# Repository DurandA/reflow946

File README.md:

# Reflow946

The Reflow946 is a Bluetooth LE temperature controller for the 946C electronic hot plate. Using this controller, a reflow profile can be programmed from your web browser using the [Web Bluetooth](https://webbluetoothcg.github.io/web-bluetooth/) API. You can use preset profiles (e.g. for lead-free or leaded soldering) or create a custom profile for a perfect cheese fondue. 🫕

The controller board is intended to replace the original controller board. It is **only compatible with the 3 buttons variant** pictured above (see this [teardown](https://youtu.be/Gv2sRJ9y_Ok)). Please send a PR if you adapted the design to a new variant.

## Hardware

The controller is based on a ESP32 module with an IPEX antenna. Since the metal case acts as a Faraday cage, the BLE signal can be improved by taping an antenna outside of the case.

### Front

### Back

## Status

- [x] Temperature control
  - [x] Temperature control using the front panel
  - [x] [BLE GATT service](https://github.com/DurandA/reflow946-firmware/wiki/GATT-Services) for temperature control
- [x] Reflow profile programming
  - [x] [BLE GATT service](https://github.com/DurandA/reflow946-firmware/wiki/GATT-Services) for reflow profiles
  - [x] [Web Bluetooth application](https://duranda.github.io/reflow946/)

## Credits

* Arnaud Durand - Orignal design
* Elías Rodríguez Martín - Revision 1.1, conversion to KiCad

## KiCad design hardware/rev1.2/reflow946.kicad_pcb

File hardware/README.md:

# Hardware

The Reflow946 hardware design is available on [https://easyeda.com/DurandA/reflow](https://easyeda.com/DurandA/reflow).

Contributions in converting the project to KiCad are welcome.

## Revision 1.0

### ESP32 module variants

⚠️ There are 85°C and 105°C variants of the ESP32-WROOM-32U(E) module. When heating stuff with a large termal mass, the temperature inside the case can largely exceed 85°C, causing glitches and reboots of the ESP32. It is advised to use the H version of the module.

### BOM

| Name | Designator | Footprint | Quantity | Supplier |
|---|---|---|---|---|
| MOC3041M | U1 | DIP-6_L8.5-W6.4-P2.54-LS7.6-BL | 1 | [LCSC](https://lcsc.com/product-detail/C8921.html) |
| ESP32-WROOM-32UE-H4 | U2 | WIFIM-SMD_39P-L19.2-W18.0-P1.27 | 1 | [LCSC](https://lcsc.com/product-detail/C3013922.html) |
| MAX31855KASA | U3 | SO-8_L4.9-W3.9-P1.27-LS5.9-BL | 1 | [LCSC](https://lcsc.com/product-detail/C52028.html) |
| AMS1117-3.3 | U4 | SOT-223-3_L6.5-W3.4-P2.30-LS7.0-BR | 1 | [LCSC](https://lcsc.com/product-detail/C6186.html) |
| ~EL817~ | U5 | SOP-4_L6.5-W4.6-P2.54-LS10.2-TL | ~1~ | ~[LCSC](lcsc.com/product-detail/C183799.html)~ |
| 100nF | CBB1 | CAP-TH_L13.0-W6.0-P10.00-D1.2 | 1 | [LCSC](https://lcsc.com/product-detail/C105712.html) |
| 1000uF/25V | C1 | CAP-D10.0×F5.0 | 1 |  |
| 10u | C2,C3 | C0805 | 2 |  |
| 0.01u | C4 | C0603 | 1 |  |
| 10u | C5 | C0603 | 1 |  |
| 0.1u | C6 | C0603 | 1 |  |
| MB6F | D1 | MBF_L4.8-W3.9-P2.50-LS6.7-BL | 1 | [LCSC](https://lcsc.com/product-detail/C2490.html) |
| SM4007PL | D2 | SOD-123F_L2.8-W1.8-LS3.7-RD | 1 | [LCSC](https://lcsc.com/product-detail/C64898.html) |
| HDR-M-2.54_2x3 | ESP-PROG | HDR-M-2.54_2X3 | 1 | [LCSC](https://lcsc.com/product-detail/C65114.html) |
| SMD0805-020-16V | F1 | F0805 | 1 | [LCSC](https://lcsc.com/product-detail/C70057.html) |
| ~CBG100505U260T~ | L1,L2 | L0402 | ~2~ | ~[LCSC](https://lcsc.com/product-detail/C668229.html)~ |
| 3bit common anode 0.4" LED segment display | LED1 | LED-SEG-TH_12P-L30.1-W16.0-P2.54-S12.70-BL | 1 | [LCSC](https://lcsc.com/product-detail/C105656.html) |
| VH-2A | P1 | CONN-TH_VH3.96-2A | 1 | [LCSC](https://lcsc.com/product-detail/C16728.html) |
| VH3.96-3P2 | P2,P3 | CONN-TH_VH3.96-3P2 | 2 | [LCSC](https://lcsc.com/product-detail/C18157.html) |
| XH-2A | P4 | CONN-TH_XH-2A | 1 | [LCSC](https://lcsc.com/product-detail/C20079.html) |
| BTA16-600BRG | Q1 | TO-220-3_L10.0-W4.5-P2.54-L | 1 | [LCSC](https://lcsc.com/product-detail/C9100.html) |
| MMBT3904 | Q2,Q3,Q4 | SOT-23-3_L2.9-W1.3-P1.90-LS2.4-BR | 3 | [LCSC](https://lcsc.com/product-detail/C20526.html) |
| 220 | R1,R10,R11,R12,R13,<br>R14,R15,R16,R17 | R0603 | 9 |  |
| ~1k~ | R2,R21 | R0603 | ~2~ |  |
| 30 | R3 | R_AXIAL-0.5 | 1 |  |
| 330 | R4 | R_AXIAL-0.5 | 1 |  |
| 100R/2W | R5 | R_AXIAL-0.6 | 1 |  |
| 10k | R6,R8 | R0603 | 2 |  |
| D6C40F1LFS | SW1,SW2,SW3 | | 3 | [LCSC](https://lcsc.com/product-detail/C2689630.html) |
| uFL antenna | | | 1 | [AliExpress](https://aliexpress.com/item/4000044880454.html) |

Ferrite beads (`L1`, `L2`) are not really required, you can make a solder bridge.

### Errata

- ⚠️ `U3` (_MAX31855KASA_) has [reverse polarity on K element](https://github.com/DurandA/reflow946/issues/7) and [`MISO` and `CLK` pins are swapped](https://github.com/DurandA/reflow946/issues/6) on revision 1.1.
- Zero-cross detection circuitry is not required with the use of the MOC3041 and will be removed in future revisions of the board. You do not need to populate `U5`, `R2`, `R21` and you can use a 0Ω resistor over `D2` footprint.

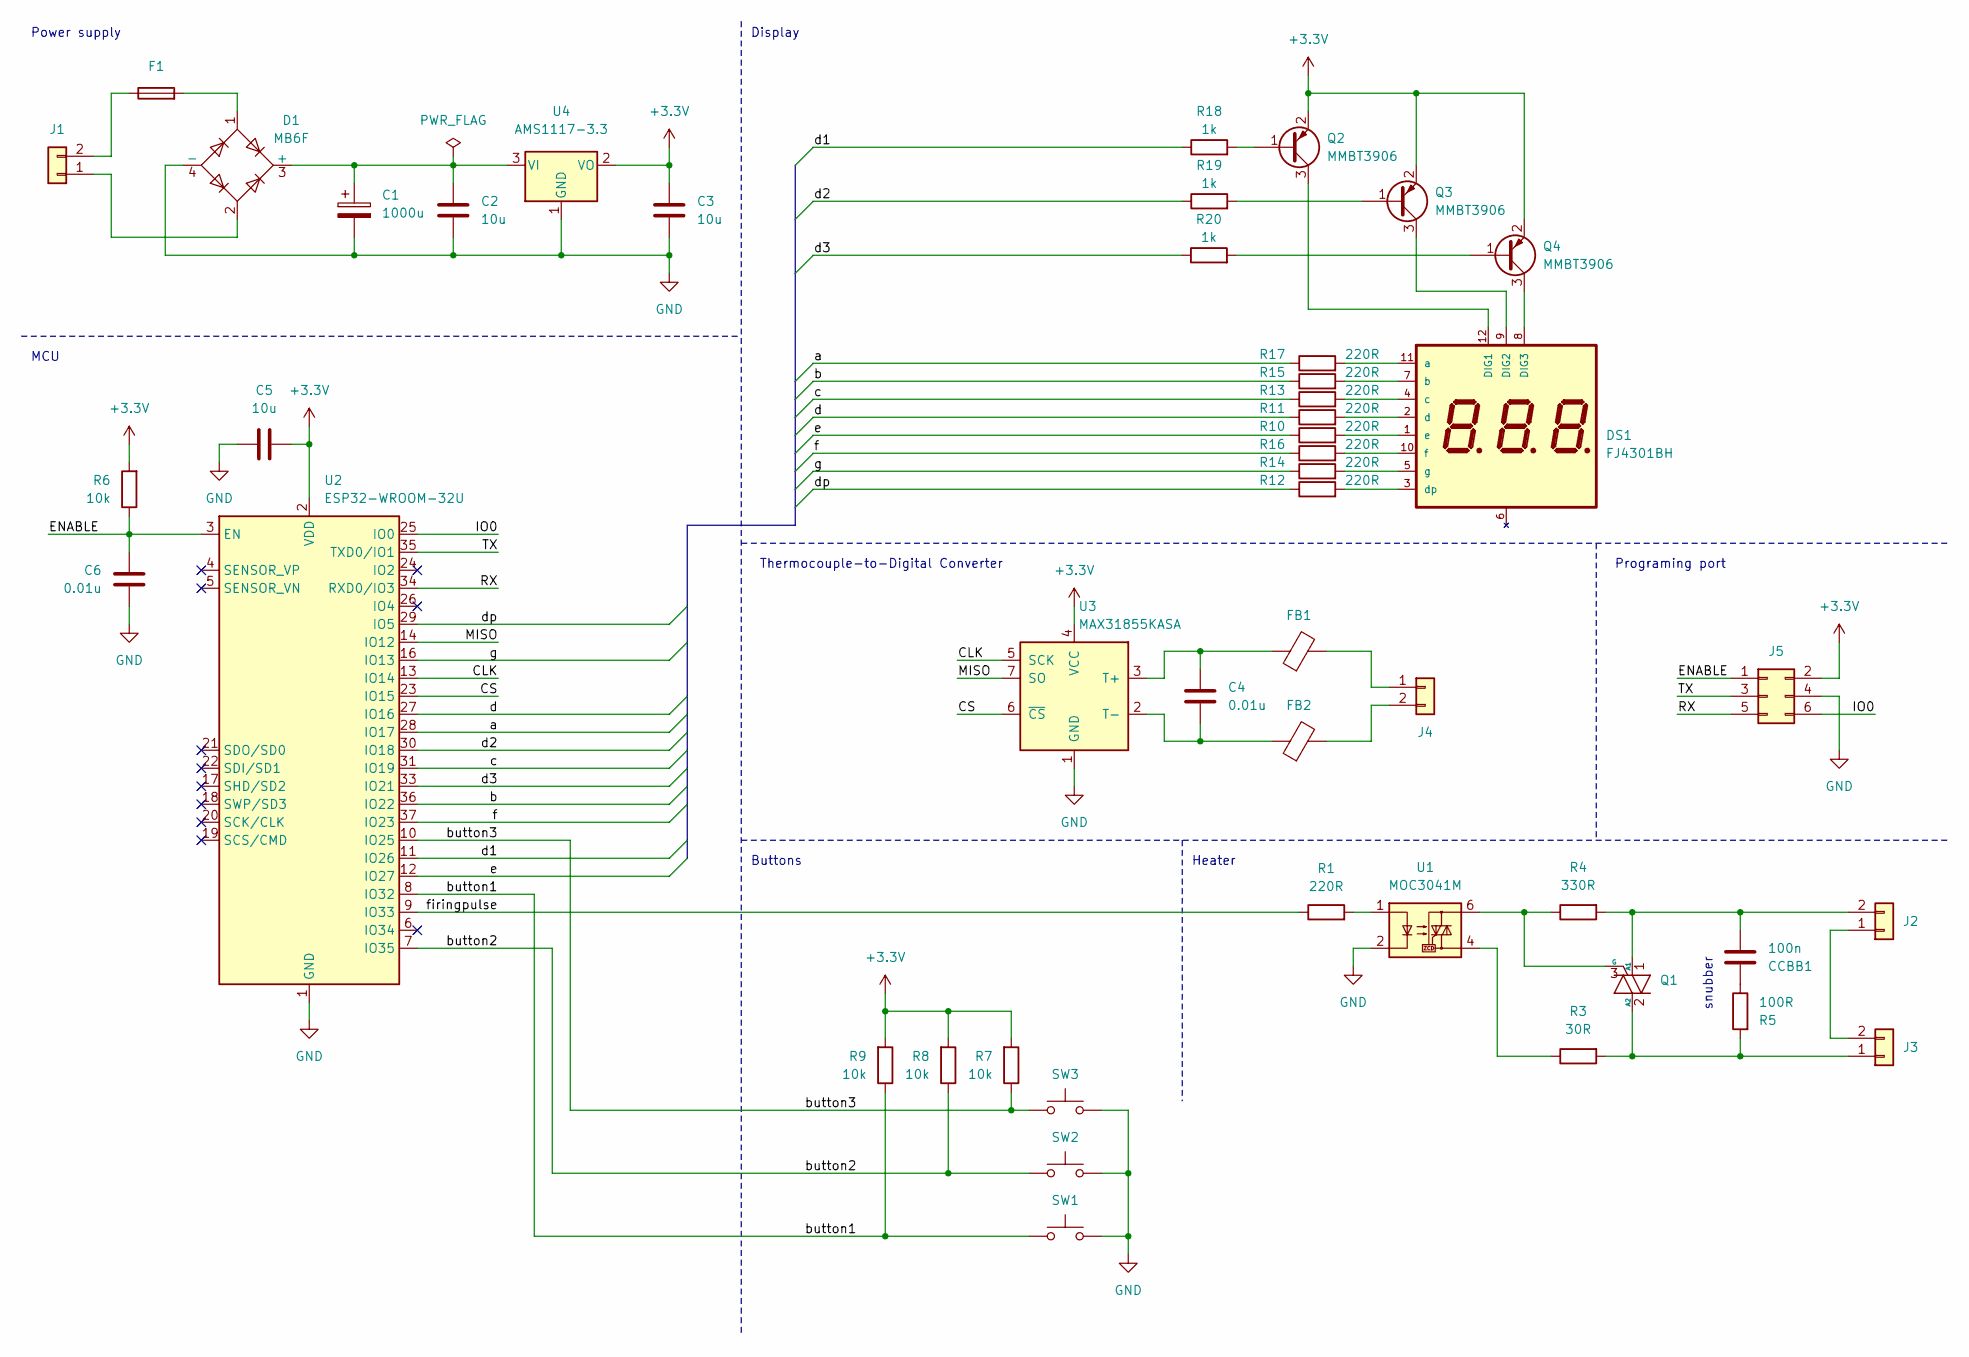
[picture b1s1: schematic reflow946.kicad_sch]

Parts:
C1: 1000u; CP_Radial_D10.0mm_P5.00mm
C2, C3, C5: 10u; C_0805_2012Metric_Pad1.18x1.45mm_HandSolder
C4, C6: 0.01u; C_0805_2012Metric_Pad1.18x1.45mm_HandSolder
CCBB1: 100n; C_Rect_L13.0mm_W6.0mm_P10.00mm_FKS3_FKP3_MKS4; Part Number MP1104K44C3R6LC; LCSC Part # C105712
D1: MB6F; MB-F; Part Number MB6F; LCSC Part # C2490
DS1: FJ4301BH; Part Number C10706; LCSC Part # C10706
F1: SMD0805-020-16V; Fuse_0805_2012Metric_Pad1.15x1.40mm_HandSolder; Part Number SMD0805-020-16V; LCSC Part # C70057
FB1, FB2: FerriteBead; R_0603_1608Metric_Pad0.98x0.95mm_HandSolder
J1: VH-2A; JST_VH_B2P-VH_1x02_P3.96mm_Vertical; Part Number VH-2A; LCSC Part # C16728
J2, J3: VH-3A2; JST_VH_B2P3-VH_1x02_P7.92mm_Vertical; Part Number VH-3A2; LCSC Part # C18157
J4: XH-A2; CONN-TH_XH-2A; Part Number XH-2A; LCSC Part # C20079
J5: HDR-M-2.54_2x3; PinHeader_2x03_P2.54mm_Vertical; Part Number C65114; LCSC Part # C65114
Q1: BTA16-600BRG; TO-220-3_Horizontal_TabUp; Part Number BTA16-600BRG; LCSC Part # C9100
Q2, Q3, Q4: MMBT3906; SOT-23; Part Number MMBT3906; LCSC Part # C181120
R1, R10, R11, R12, R13, R14, R15, R16, R17: 220R; R_0603_1608Metric_Pad0.98x0.95mm_HandSolder
R3: 30R; R_Axial_DIN0309_L9.0mm_D3.2mm_P12.70mm_Horizontal
R4: 330R; R_Axial_DIN0309_L9.0mm_D3.2mm_P12.70mm_Horizontal
R5: 100R; R_Axial_DIN0414_L11.9mm_D4.5mm_P15.24mm_Horizontal
R6, R7, R8, R9: 10k; R_0603_1608Metric_Pad0.98x0.95mm_HandSolder
R18, R19, R20: 1k; R_0603_1608Metric_Pad0.98x0.95mm_HandSolder
SW1, SW2, SW3: SW_Push; SW-TH_D6C10F1LFS; Part Number D6C40F1LFS; LCSC Part # C2689630
U1: MOC3041M; DIP-6_W7.62mm_LongPads; Part Number MOC3041M; LCSC Part # C8921
U2: ESP32-WROOM-32U; Part Number ESP32-WROOM-32U-H4; LCSC Part # C3013938
U3: MAX31855KASA; SOIC-8_3.9x4.9mm_P1.27mm; Part Number MAX31855KASA+T; LCSC Part # C52028
U4: AMS1117-3.3; SOT-223-3_TabPin2; Part Number AMS1117-3.3; LCSC Part # C6186

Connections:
+3.3V: C3.1, C5.2, J5.2, Q2.2 (E), Q3.2 (E), Q4.2 (E), R6.2, R7.2, R8.2, R9.2, U2.2 (VDD), U3.4 (VCC), U4.2 (VO)
/CLK: U2.13 (IO14), U3.5 (SCK)
/CS: U2.23 (IO15), U3.6 (~CS)
/ENABLE: C6.2, J5.1, R6.1, U2.3 (EN)
/IO0: J5.6, U2.25 (IO0)
/MISO: U2.14 (IO12), U3.7 (SO)
/RX: J5.5, U2.34 (RXD0/IO3)
/TX: J5.3, U2.35 (TXD0/IO1)
/a: R17.1, U2.28 (IO17)
/b: R15.1, U2.36 (IO22)
/button1: R9.1, SW1.1, U2.8 (IO32)
/button2: R8.1, SW2.1, U2.7 (IO35)
/button3: R7.1, SW3.1, U2.10 (IO25)
/c: R13.1, U2.31 (IO19)
/d: R11.1, U2.27 (IO16)
/d1: R18.1, U2.11 (IO26)
/d2: R19.1, U2.30 (IO18)
/d3: R20.1, U2.33 (IO21)
/dp: R12.1, U2.29 (IO5)
/e: R10.1, U2.12 (IO27)
/f: R16.1, U2.37 (IO23)
/firingpulse: R1.1, U2.9 (IO33)
/g: R14.1, U2.16 (IO13)
GND: C1.2, C2.2, C3.2, C5.1, C6.1, D1.4 (-), J5.4, SW1.2, SW2.2, SW3.2, U1.2, U2.1 (GND), U2.15 (GND), U2.38 (GND), U2.39 (GND), U3.1 (GND), U4.1 (GND)
unnamed: CCBB1.1, R5.1
unnamed: C1.1, C2.1, D1.3 (+), U4.3 (VI)
unnamed: D1.1, F1.2
unnamed: DS1.12 (DIG1), Q2.3 (C)
unnamed: DS1.9 (DIG2), Q3.3 (C)
unnamed: DS1.8 (DIG3), Q4.3 (C)
unnamed: DS1.11 (a), R17.2
unnamed: DS1.7 (b), R15.2
unnamed: DS1.4 (c), R13.2
unnamed: DS1.2 (d), R11.2
unnamed: DS1.3 (dp), R12.2
unnamed: DS1.1 (e), R10.2
unnamed: DS1.10 (f), R16.2
unnamed: DS1.5 (g), R14.2
unnamed: D1.2, J1.1
unnamed: F1.1, J1.2
unnamed: J2.1, J3.2
unnamed: CCBB1.2, J2.2, Q1.1 (A1), R4.2
unnamed: J3.1, Q1.2 (A2), R3.2, R5.2
unnamed: FB1.2, J4.1
unnamed: FB2.2, J4.2
unnamed: Q1.3 (G), R4.1, U1.6
unnamed: Q2.1 (B), R18.2
unnamed: Q3.1 (B), R19.2
unnamed: Q4.1 (B), R20.2
unnamed: R1.2, U1.1
unnamed: R3.1, U1.4
unnamed: C4.1, FB1.1, U3.3 (T+)
unnamed: C4.2, FB2.1, U3.2 (T-)

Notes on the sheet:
Power supply
Programing port
Thermocouple-to-Digital Converter
snubber
MCU
Heater
Display
Buttons

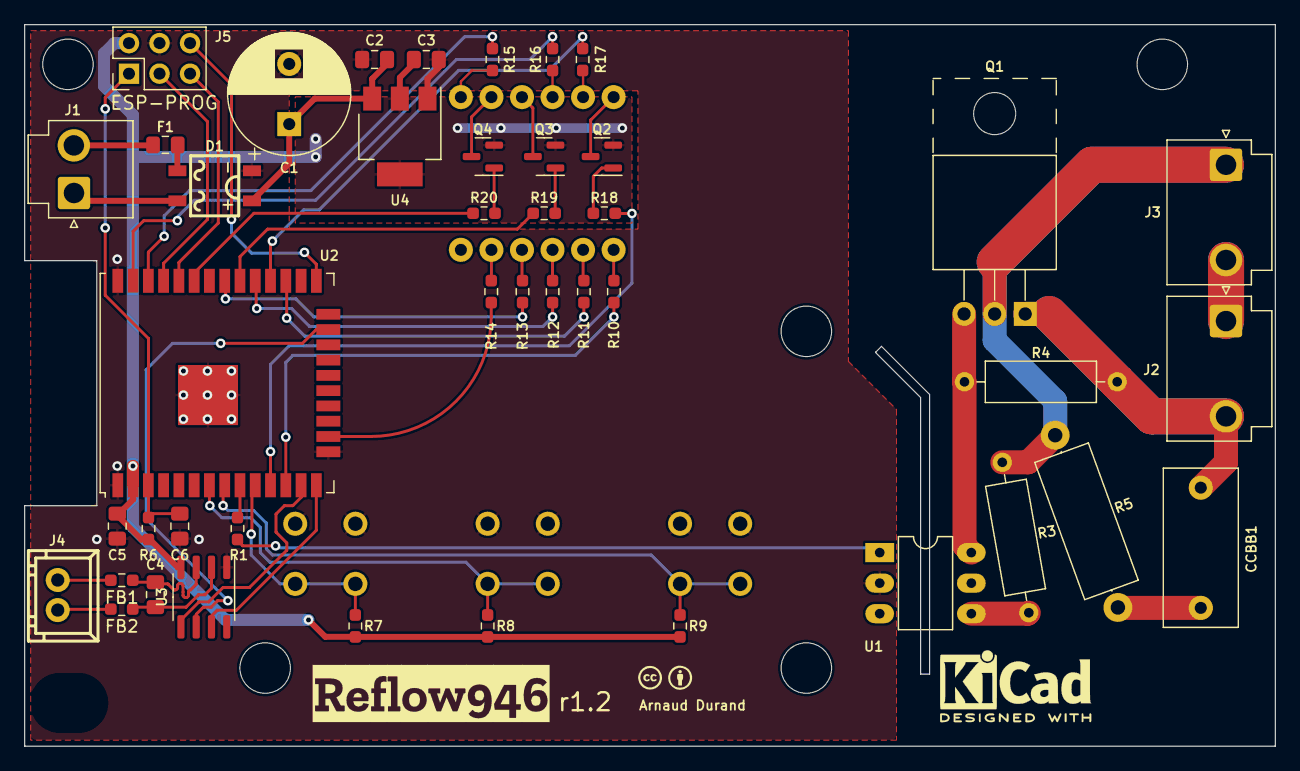
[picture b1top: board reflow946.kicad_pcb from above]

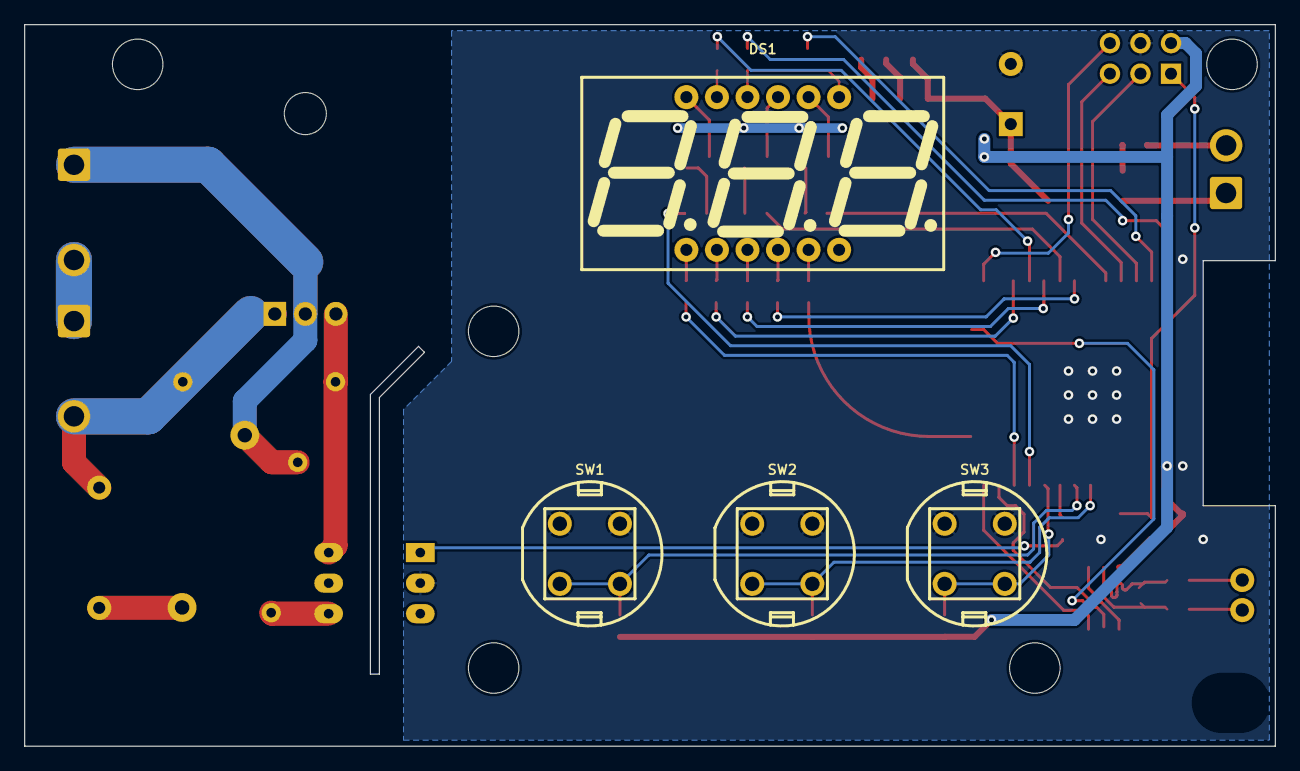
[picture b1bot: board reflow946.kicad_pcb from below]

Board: 2 copper layers, 104.0 x 60.0 mm, 48 parts (4 on the bottom side), 53 nets.

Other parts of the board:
kibuzzard-632CED8E: G***; kibuzzard-632CED8E

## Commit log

2021-02-01 Add hardware docs
2021-02-01 Add README
2021-03-17 Update firmware
2022-09-11 Link GATT services in wiki
2022-09-17 Add python example
2022-09-18 Add gerber files of rev1.0
2022-09-18 Update hardware README
2022-09-19 Update BOM
2022-09-22 Add CC-BY-4.0 license
2022-09-23 Migrate project to KiCad v6.x
    First attempt at migrating the project from easyeda to KiCad v6.x.
    This version should be fully compatible with current firmware, execpt
    for DS1 annode driving, that should be inverted if MMBT3906 is used in
    place of MMBT3904.
    Note: Not including 3D models from firth parties, as they might have
    incompatible licences.
2022-09-23 Fix wrong pinout on push buttons
    Leaving pull up resistor footprints in place, so they can be populated
    if needed.
2022-09-24 Address PR comments
    Remove cache files
    Update .gitignore
    Rename reflow946.pdf to schematics.pdf
    Remove schematics.jpg
    Add thermal reliefs to SMD pads connected to planes to make soldering
    easier
2022-09-24 Migrate project to KiCad v6.x
    First attempt at migrating the project from easyeda to KiCad v6.x.
    This version should be fully compatible with current firmware, execpt
    for DS1 annode driving, that should be inverted if MMBT3906 is used in
    place of MMBT3904.
    Note: Not including 3D models from firth parties, as they might have
    incompatible licences.
2022-09-24 Add credits
2022-09-24 Fix PNP transistors missplacement
2022-09-25 Assign standard 3D model to MB6F
2022-09-25 Use 0603 ferrite beads
2022-09-25 Move kicad folder to rev1.1
2022-09-26 Link Espressif KiCad library
2022-09-26 Add CH455G symbol
2023-02-01 Web build
2023-02-01 Add webapp link
2024-05-04 Warn about ESP32 module version
2024-05-04 Change segment display reference
2024-05-05 Add swapped pins (rev 1.1) in errata
2024-05-05 Upgrade project to KiCad 8.0
2024-05-05 Swap MAX31855 pins
